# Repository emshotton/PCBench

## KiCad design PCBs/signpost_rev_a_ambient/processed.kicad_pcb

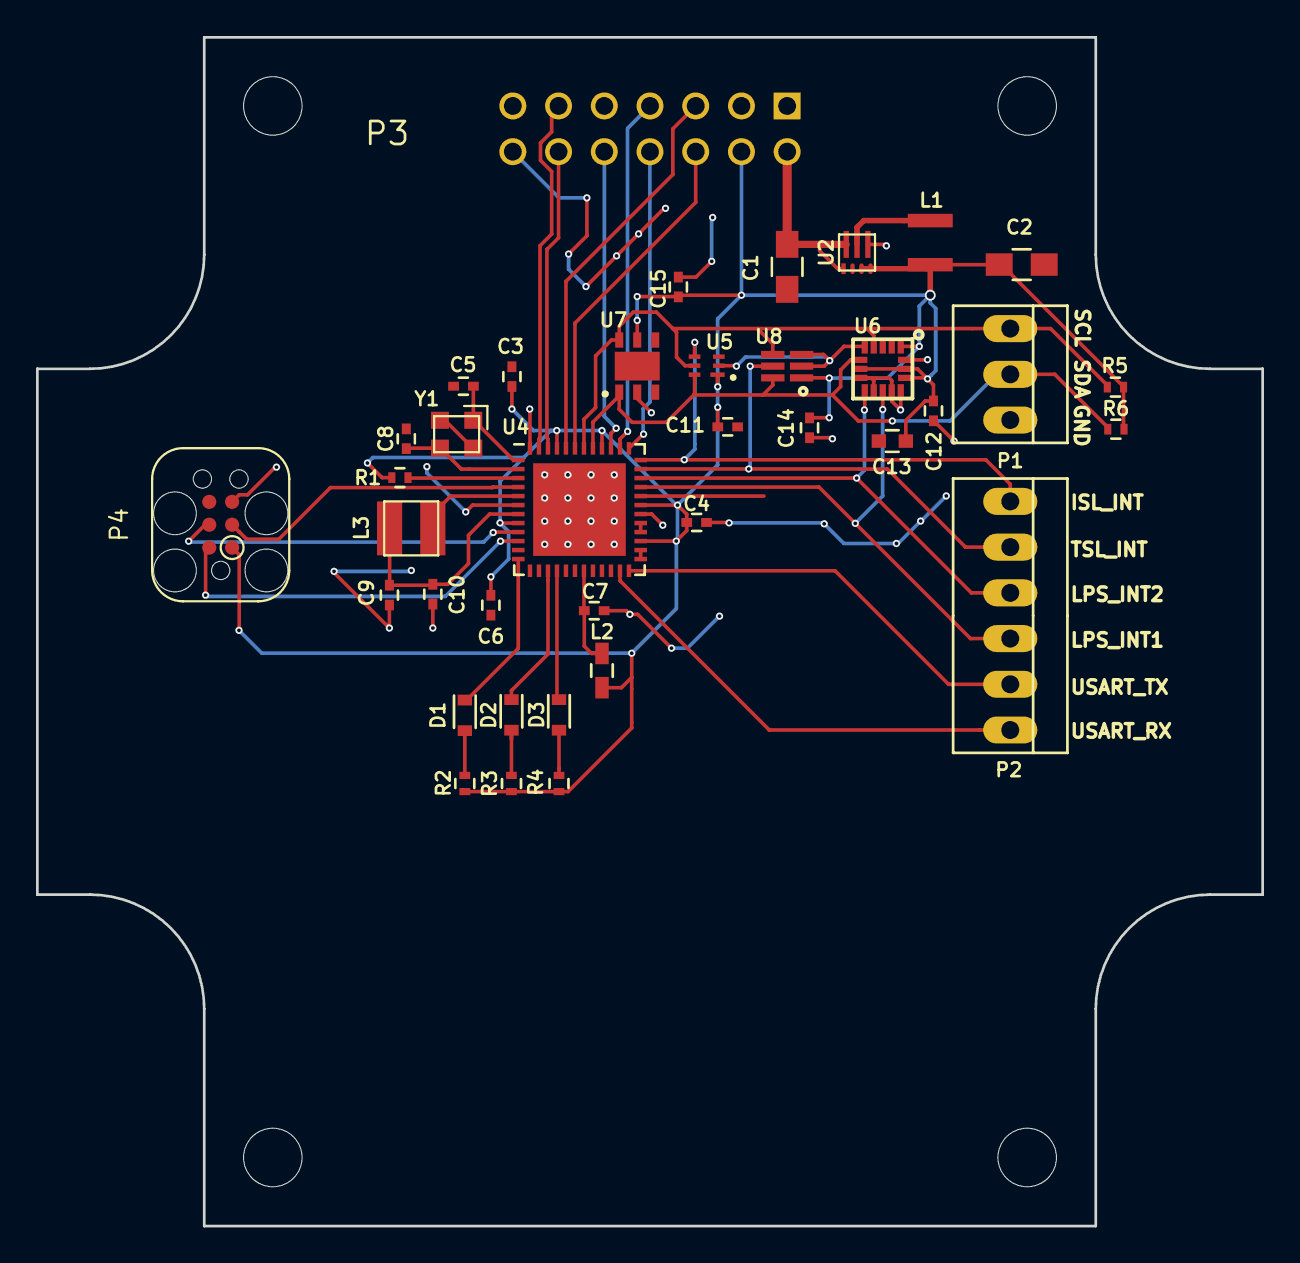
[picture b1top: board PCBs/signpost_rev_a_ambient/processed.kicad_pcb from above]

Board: 2 copper layers, 68.1 x 66.0 mm, 42 parts (0 on the bottom side), 36 nets.

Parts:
C1, C2: GENERIC_C_0805; C_0805_HandSoldering
C3, C4, C6, C7, C10, C11, C12, C14, C15: C_0.1u_0402_10V_10%_JB; C_0402
C5, C8: GENERIC_C_0402; C_0402
C9: C_4.7u_0402_10V_10%_X5R; C_0402
C13: C_10u_0603_10V_10%_JB; C_0603
D1, D2, D3: LED; D_0603
H1, H2, H3, H4: SIGNPOST_HOLE
L1: .47 uH; DFE322512C
L2: 1.5k Ohm; C_0603_HandSoldering
L3: 22uH; 1212
P1: CONN_01X03; PINHEAD1-3
P2: CONN_01X06; PINHEAD1-6
P3: SIGNPOST_MODULE_GENERIC
P4: JLINK-TC; TC2030-IDC
R1: R_10k_0402_1%,100ppm/c,0.063W; R_0402
R2, R3, R4, R5, R6: GENERIC_R_0402; R_0402
U2: TPS62086; RLT0007A
U4: SAM4LC8A; QFN-48-1EP_7x7mm_Pitch0.5mm
U5: ISL29035; L6_1.5x1.6mm
U6: LPS331AP; HCLGA-16L
U7: Si7021; DFN_3x3mm_1mm
U8: TSL2561; DFN2
Y1: FH1600015; FHXXX

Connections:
+3V3: C2.1, C3.1, C4.1, C6.1, C11.1, C12.1, C13.1, C14.1, C15.1, L1.1, L2.2, P3.4, P4.1, R1.1, R2.2, R3.2, R4.2, R5.1, R6.1, U2.3, U2.4, U4.8, U4.27, U4.31, U4.40, U4.45, U5.1, U6.1, U6.7, U6.14, U6.15, U7.5, U8.1
+5V: C1.1, P3.2, U2.1, U2.7
/CNTR_PPS: P3.7, U4.38
/CNTR_SCL: P3.5, U4.44
/CNTR_SDA: P3.6, U4.43
/ISL_INT: P2.1, U4.36, U5.4
/LED_1: D1.1, U4.12
/LED_2: D2.1, U4.15
/LED_3: D3.1, U4.16
/LPS_INT1: P2.4, U4.33, U6.11
/LPS_INT2: P2.3, U4.34, U6.9
/MOD_IN: P3.10, U4.39
/MOD_OUT: P3.8, U4.37
/SAM4L_RESET: P4.3, U4.4
/SAM4L_SWDCLK: P4.4, U4.9
/SAM4L_SWDIO: P4.2, U4.10
/TSL_INT: P2.2, U4.35, U8.5
/USART_RX: P2.6, U4.23
/USART_TX: P2.5, U4.24
/USB_D+: P3.11, U4.47
/USB_D-: P3.12, U4.46
/VDDANA: C7.1, L2.1, U4.19
/VDD_CORE: L3.1, U4.5
/VDD_OUT: C9.1, C10.1, L3.2, U4.7
/xin: C5.1, U4.1, Y1.1
/xout: C8.1, U4.2, Y1.3
GND: C1.2, C2.2, C3.2, C4.2, C5.2, C6.2, C7.2, C8.2, C9.2, C10.2, C11.2, C12.2, C13.2, C14.2, C15.2, P1.3, P3.1, P3.14, P4.5, U2.5, U4.6, U4.17, U4.30, U4.48, U4.49, U5.2, U6.5, U6.8, U6.10, U6.12, U6.13, U6.16, U7.2, U8.2, U8.3, Y1.2, Y1.4
unnamed: D1.2, R2.1
unnamed: D2.2, R3.1
unnamed: D3.2, R4.1
unnamed: L1.2, U2.6
unnamed: R1.2, U4.3
unnamed: U4.25, U4.26
unnamed: U4.28, U4.29
SCL: P1.1, R5.2, U4.42, U5.5, U6.4, U7.6, U8.4
SDA: P1.2, R6.2, U4.41, U5.6, U6.6, U7.1, U8.6

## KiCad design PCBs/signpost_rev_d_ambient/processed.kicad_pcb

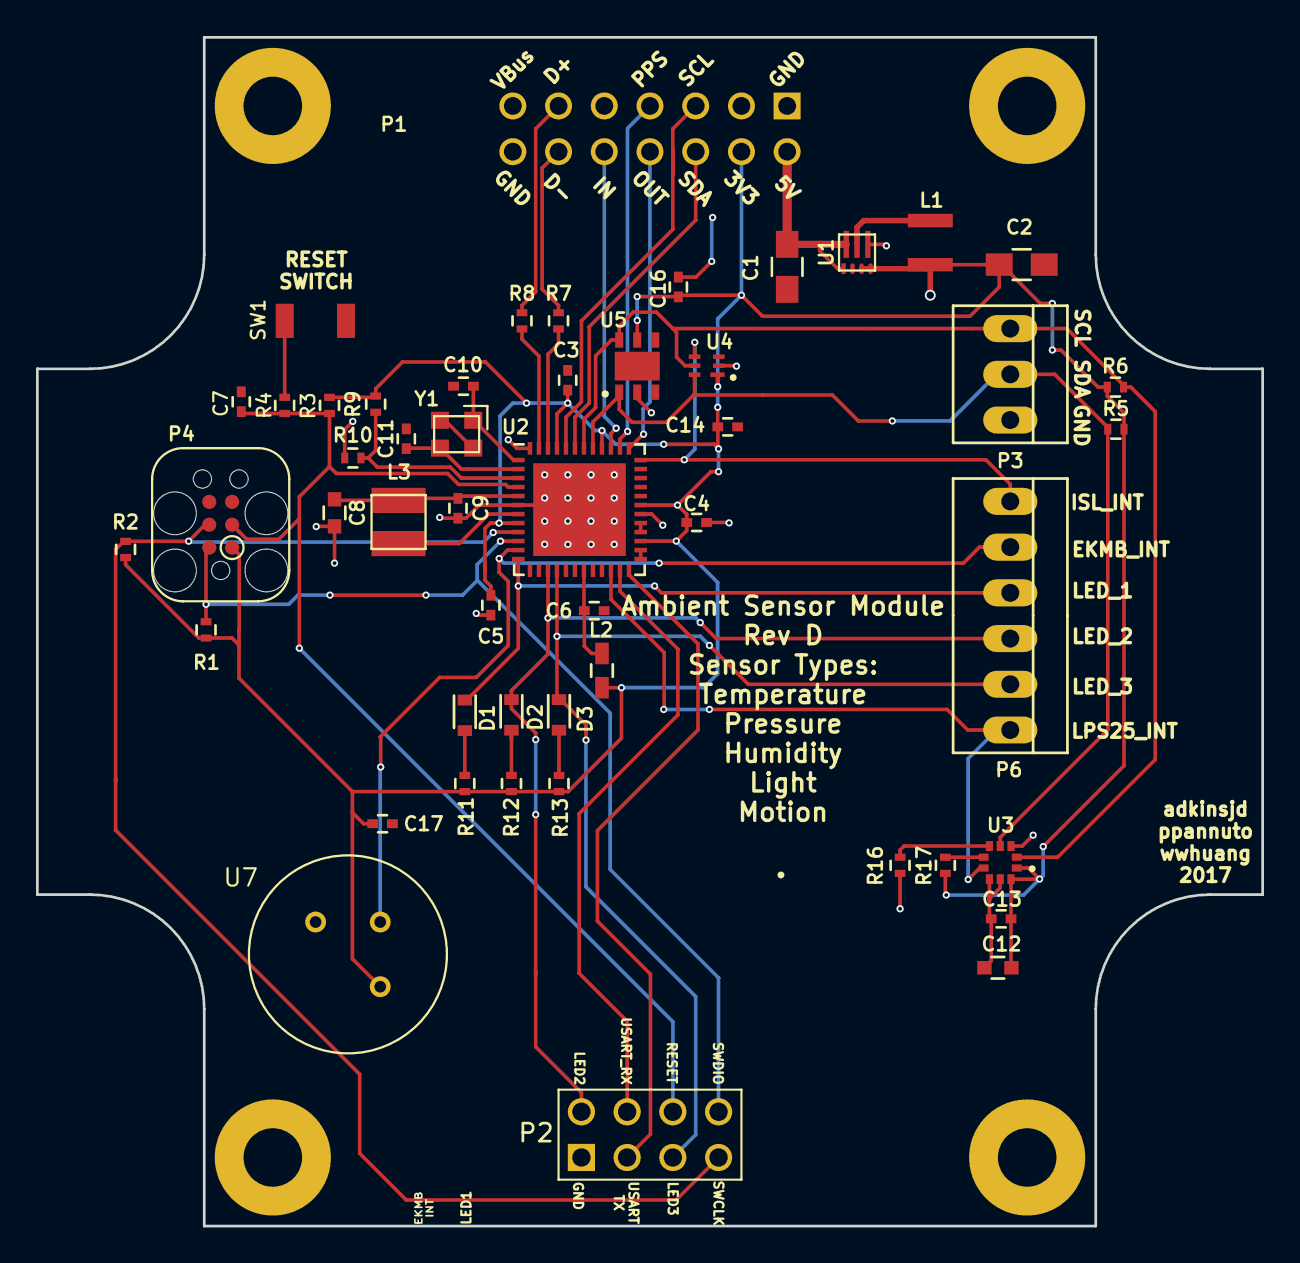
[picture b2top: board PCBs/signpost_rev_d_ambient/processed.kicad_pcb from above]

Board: 2 copper layers, 68.1 x 66.0 mm, 54 parts (0 on the bottom side), 40 nets.

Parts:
C1, C2: GENERIC_C_0805; C_0805_HandSoldering
C3, C4, C5, C6, C9, C13, C14, C16, C17: C_0.1u_0402_10V_10%_JB; C_0402
C7, C10, C11: GENERIC_C_0402; C_0402
C8: GENERIC_C_0603; C_0603
C12: C_10u_0603_10V_10%_JB; C_0603
D1, D2, D3: LED; D_0603
H1, H2, H3, H4: SIGNPOST_HOLE
L1: .47 uH; DFE322512C
L2: 1.5k Ohm; C_0603_HandSoldering
L3: 22uH; 1212
P1: SIGNPOST_MODULE_GENERIC
P2: CONN_02X04; PINHEAD2-4
P3: CONN_01X03; PINHEAD1-3
P4: JLINK-TC; TC2030-IDC
P6: CONN_01X06; PINHEAD1-6
R1, R2, R3, R16, R17: R_100K_0402_0.5%,25ppm/c,0.063W; R_0402
R4: GENERIC_R_0402; R_0402
R5, R6, R9: R_10k_0402_1%,100ppm/c,0.063W; R_0402
R7, R8: R_39_0402_1%,100ppm/c,0.063W; R_0402
R10: R_0_0402_.1W; R_0402
R11, R12, R13: R_1K_0402_1%,100ppm/c,0.2W; R_0402
SW1: BSU-1000P; B3U-1000p
U1: TPS62086; RLT0007A
U2: SAM4LC8A; QFN-48-1EP_7x7mm_Pitch0.5mm
U3: LPS25HB; HLGA-10L_2.5x2.5mm
U4: ISL29035; L6_1.5x1.6mm
U5: Si7021; DFN_3x3mm_1mm
U7: EKMB1101111
Y1: FH1600015; FHXXX

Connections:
+3V3: C2.1, C3.1, C4.1, C5.1, C12.1, C13.1, C14.1, C16.1, C17.1, L1.1, L2.2, P1.4, P4.1, R1.2, R2.1, R3.1, R5.1, R6.1, R9.1, R11.2, R12.2, R13.2, R17.1, U1.3, U1.4, U2.8, U2.27, U2.31, U2.40, U2.45, U3.1, U3.10, U4.1, U5.5, U7.2
+5V: C1.1, P1.2, U1.1, U1.7
/CNTR_PPS: P1.7, U2.38
/CNTR_SCL: P1.5, U2.44
/CNTR_SDA: P1.6, U2.43
/EKMB_INT: P6.2, U2.11, U7.1
/ISL_INT: P6.1, U2.36, U4.4
/LED_1: D1.1, P6.3, U2.12
/LED_2: D2.1, P2.2, P6.4, U2.15
/LED_3: D3.1, P2.5, P6.5, U2.16
/LPS25_INT: P6.6, U2.22, U3.7
/MOD_IN: P1.10, U2.39
/MOD_OUT: P1.8, U2.37
/SAM4L_RESET: C7.1, P2.6, P4.3, R3.2, R4.1, U2.4
/SAM4L_SWDCLK: P2.7, P4.4, R2.2, U2.9
/SAM4L_SWDIO: P2.8, P4.2, R1.1, U2.10
/USART_RX: P2.4, U2.23
/USART_TX: P2.3, U2.24
/USB_D+: P1.11, R8.2
/USB_D-: P1.12, R7.2
/VDDANA: C6.1, L2.1, U2.19
/VDD_CORE: C8.1, C9.1, L3.2, U2.5
/VDD_OUT: L3.1, U2.7
/sensors/LPS25_CS: R17.2, U3.6
/sensors/LPS25_SA0: R16.2, U3.5
/xin: C10.1, U2.1, Y1.1
/xout: C11.1, U2.2, Y1.3
GND: C1.2, C2.2, C3.2, C4.2, C5.2, C6.2, C7.2, C8.2, C9.2, C10.2, C11.2, C12.2, C13.2, C14.2, C16.2, C17.2, P1.1, P1.14, P2.1, P3.3, P4.5, R10.2, R16.1, SW1.2, U1.5, U2.6, U2.17, U2.30, U2.48, U2.49, U3.3, U3.8, U3.9, U4.2, U5.2, U7.3, Y1.2, Y1.4
unnamed: D1.2, R11.1
unnamed: D2.2, R12.1
unnamed: D3.2, R13.1
unnamed: L1.2, U1.6
unnamed: R4.2, SW1.1
unnamed: R7.1, U2.46
unnamed: R8.1, U2.47
unnamed: R9.2, R10.1, U2.3
unnamed: U2.25, U2.26
unnamed: U2.28, U2.29
SCL: P3.1, R6.2, U2.42, U3.2, U4.5, U5.6
SDA: P3.2, R5.2, U2.41, U3.4, U4.6, U5.1

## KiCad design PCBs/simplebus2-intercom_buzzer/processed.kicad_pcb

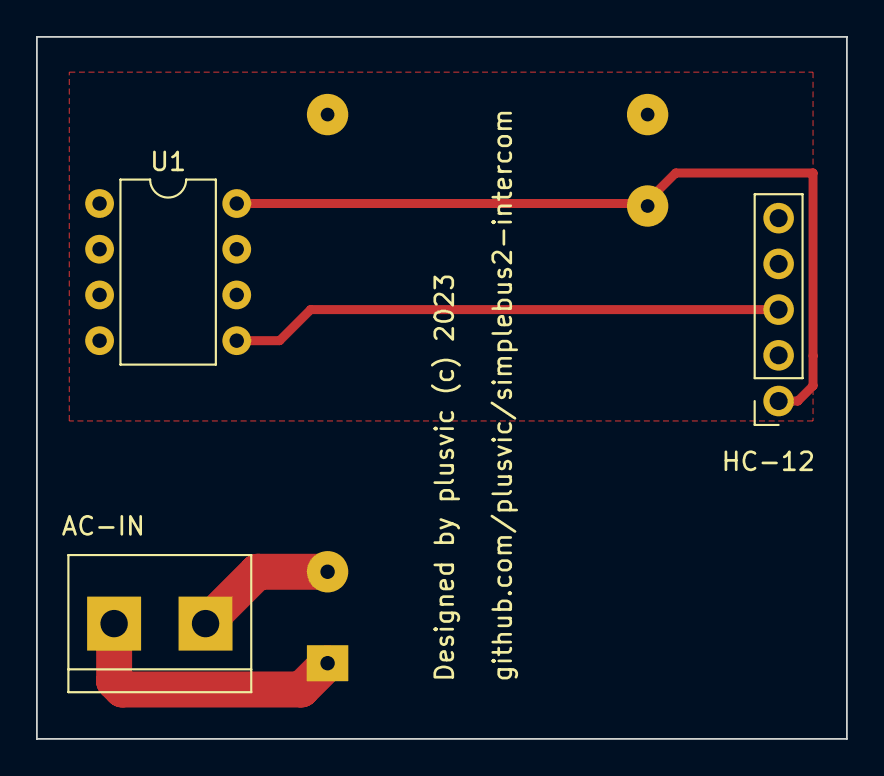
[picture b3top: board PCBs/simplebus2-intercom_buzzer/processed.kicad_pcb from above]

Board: 2 copper layers, 45.0 x 39.0 mm, 4 parts (1 on the bottom side), 5 nets.

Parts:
AC-IN: Screw_Terminal_01x02; TerminalBlock_bornier-2_P5.08mm
HC-12: Conn_01x05_Female; PinSocket_1x05_P2.54mm_Vertical
PS1: IRM-03-3.3; Custom_Converter_ACDC_MeanWell_IRM-03-xx_THT
U1: ATtiny13-20P; DIP-8_W7.62mm

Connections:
GND: HC-12.2, PS1.14 (-Vo), U1.4 (GND)
unnamed: HC-12.3, U1.5 (PB0)
unnamed: AC-IN.1, PS1.1 (AC/L)
unnamed: AC-IN.2, PS1.3 (AC/N)
Vcc: HC-12.1, PS1.16 (+Vo), U1.8 (VCC)

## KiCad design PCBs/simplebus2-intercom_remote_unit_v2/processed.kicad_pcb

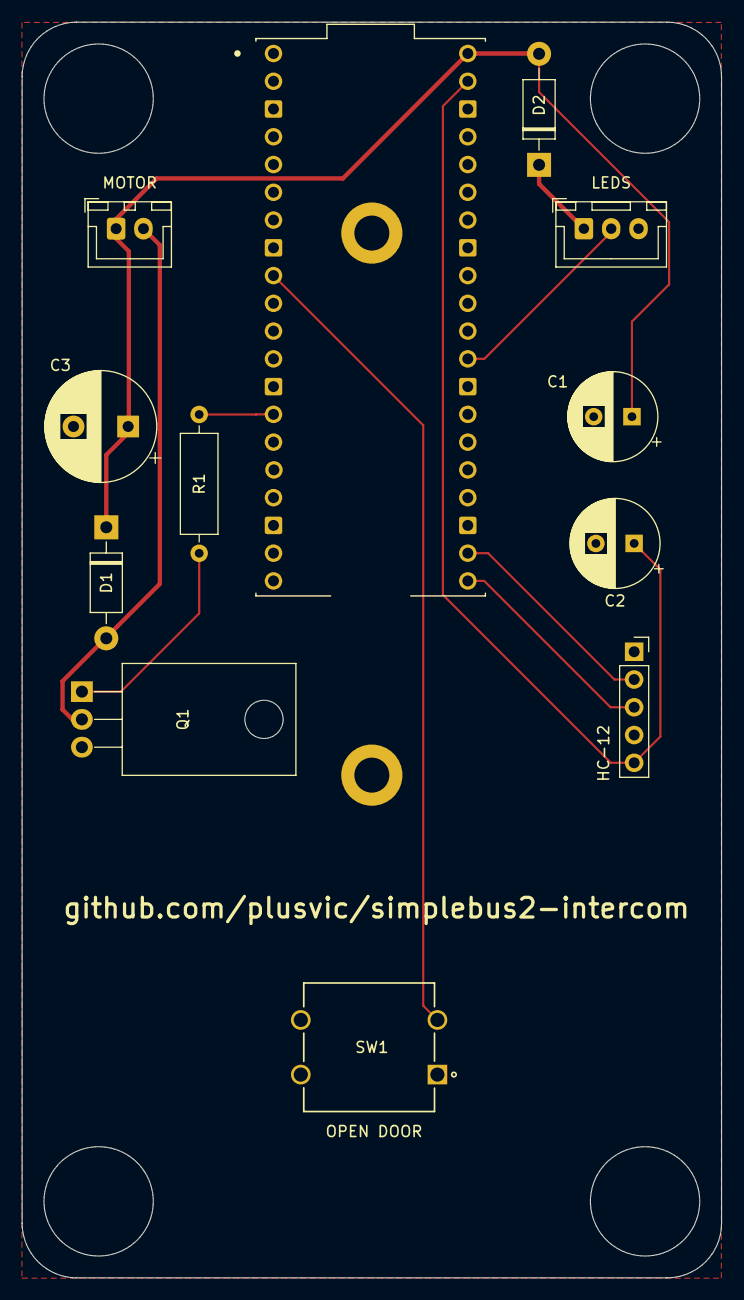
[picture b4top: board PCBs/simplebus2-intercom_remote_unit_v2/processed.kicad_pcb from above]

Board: 2 copper layers, 64.0 x 114.9 mm, 12 parts (0 on the bottom side), 11 nets.

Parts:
A1: SC0918; MODULE_SC0918
C1, C2: 470uF; CP_Radial_D8.0mm_P3.50mm
C3: 680uF; CP_Radial_D10.0mm_P5.00mm
D1, D2: 1N4001; D_DO-41_SOD81_P10.16mm_Horizontal
J1: LEDS; JST_XH_B3B-XH-A_1x03_P2.50mm_Vertical
J2: HC-12; PinSocket_1x05_P2.54mm_Vertical
J3: MOTOR; JST_XH_B2B-XH-A_1x02_P2.50mm_Vertical
Q1: Q_NPN_Darlington_BCE; TO-220-3_Horizontal_TabDown
R1: 1k; R_Axial_DIN0309_L9.0mm_D3.2mm_P12.70mm_Horizontal
SW1: OPEN DOOR; COM-10302_SPK

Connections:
3.3V: A1.39 (VSYS), C2.1, J2.5
/RX: A1.21 (GP16), J2.3
/TX: A1.22 (GP17), J2.2
GND: A1.3 (GND), A1.8 (GND), A1.13 (GND), A1.18 (GND), A1.23 (GND), A1.28 (GND), A1.33 (AGND), A1.38 (GND), C1.2, C2.2, C3.2, J1.3, J2.4, Q1.3 (E), SW1.1
unnamed: A1.9 (GP6), SW1.3 (K)
unnamed: A1.14 (GP10), R1.2
unnamed: A1.29 (GP22), J1.2
unnamed: D1.2 (A), J3.2, Q1.2 (C)
unnamed: D2.1 (K), J1.1
unnamed: Q1.1 (B), R1.1
VBUS: A1.40 (VBUS), C1.1, C3.1, D1.1 (K), D2.2 (A), J3.1

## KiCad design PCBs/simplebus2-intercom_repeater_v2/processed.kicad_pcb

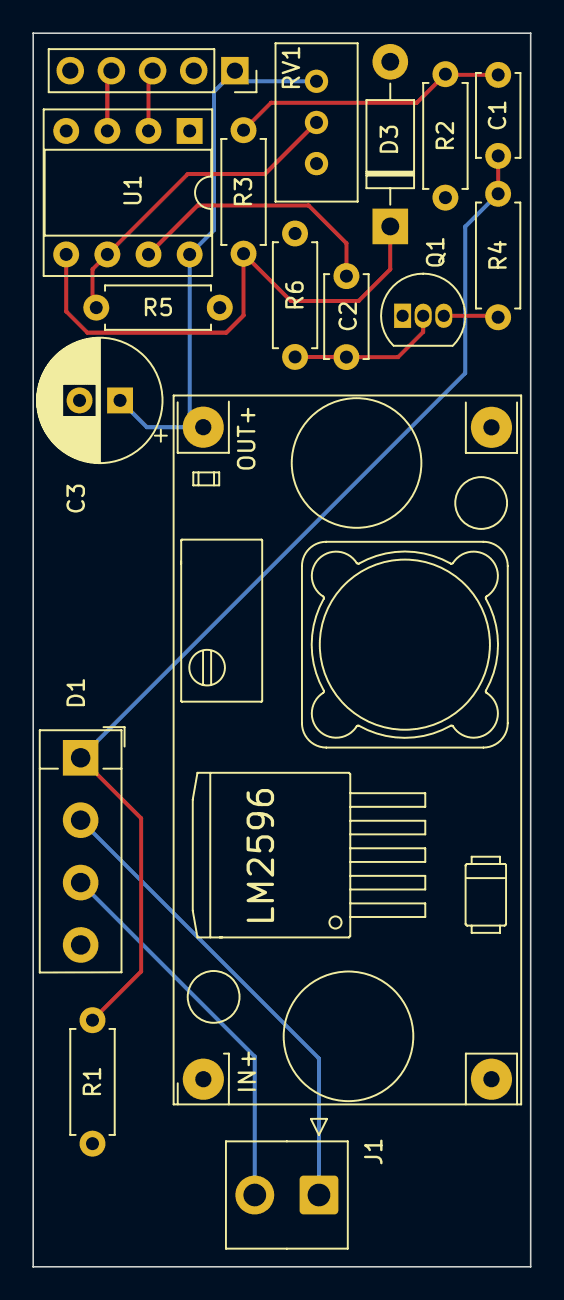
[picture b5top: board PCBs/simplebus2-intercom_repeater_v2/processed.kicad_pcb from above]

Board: 2 copper layers, 30.7 x 76.1 mm, 17 parts (0 on the bottom side), 13 nets.

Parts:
C1: 0.1uF; C_Disc_D5.0mm_W2.5mm_P5.00mm
C2: 100nF; C_Disc_D5.0mm_W2.5mm_P5.00mm
C3: 1000uF; CP_Radial_D7.5mm_P2.50mm
D1: Bridge Rectifier; Diode_Bridge_Vishay_KBPM
D3: 1N47xxA; D_DO-41_SOD81_P10.16mm_Horizontal
IN+: YAAJ_DCDC_StepDown_LM2596
J1: SimpleBus Connector; TE_826576-2_1x02_P3.96mm_Vertical
J2: HC-12; PinSocket_1x05_P2.54mm_Vertical
Q1: PN2222A; TO-92_Inline
R1: 560R; R_Axial_DIN0207_L6.3mm_D2.5mm_P7.62mm_Horizontal
R2, R5: 10k; R_Axial_DIN0207_L6.3mm_D2.5mm_P7.62mm_Horizontal
R3: 100; R_Axial_DIN0207_L6.3mm_D2.5mm_P7.62mm_Horizontal
R4: 220R; R_Axial_DIN0207_L6.3mm_D2.5mm_P7.62mm_Horizontal
R6: 2.2k; R_Axial_DIN0207_L6.3mm_D2.5mm_P7.62mm_Horizontal
RV1: 3298; Potentiometer_Bourns_3296W_Vertical
U1: ATtiny85-20P; DIP-8_W7.62mm_Socket

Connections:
+5V: C3.1, IN+.4, J2.1, RV1.1, U1.8 (VCC)
GND: C3.2, D1.4 (-), D3.2 (A), IN+.2, IN+.3, J2.2, Q1.1 (E), R2.2, R5.2, R6.2, U1.4 (GND)
unnamed: C1.2, R2.1, R3.2
unnamed: C1.1, D1.1 (+), R1.1, R4.1
unnamed: D3.1 (K), R3.1, U1.5 (AREF/PB0)
unnamed: D1.2, J1.1
unnamed: D1.3, J1.2
unnamed: C2.2, Q1.2 (B), R6.1
unnamed: Q1.3 (C), R4.2
unnamed: C2.1, U1.7 (PB2)
REF VOLTAGE: R5.1, RV1.2, U1.6 (PB1)
UART RX: J2.4, U1.3 (XTAL2/PB4)
UART TX: J2.3, U1.2 (XTAL1/PB3)

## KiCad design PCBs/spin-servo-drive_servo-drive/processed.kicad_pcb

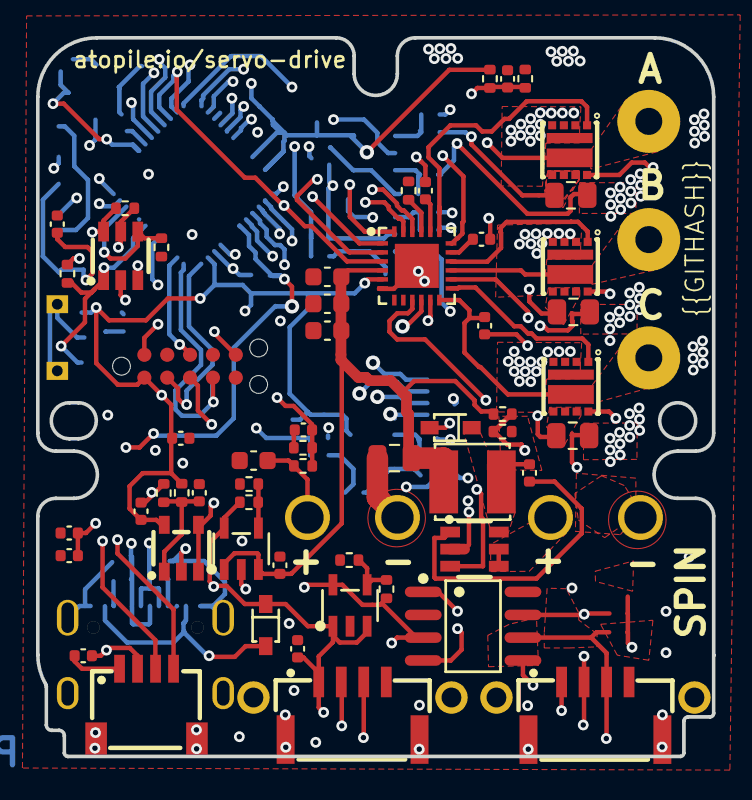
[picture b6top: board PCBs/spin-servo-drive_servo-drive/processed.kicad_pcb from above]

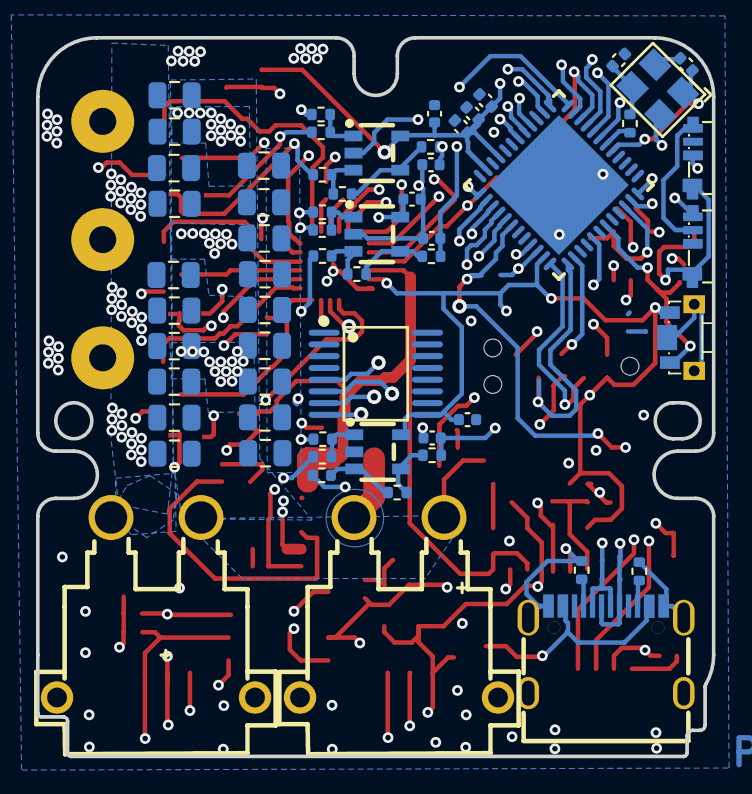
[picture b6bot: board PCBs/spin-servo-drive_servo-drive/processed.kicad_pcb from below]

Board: 4 copper layers, 37.6 x 39.9 mm, 125 parts (60 on the bottom side), 80 nets.

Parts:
C1: 10V 10uF X5R ±10% 0603 Multilayer Ceramic Capacit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; C0603
C2, C13, C16, C17, C18, C19, C24, C28, C40, C51: 16V 100nF X7R ±10% 0402 Multilayer Ceramic Capaci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; C0402
C3, C4, C6, C20, C21, C22, C25, C26, C27, C29, C30, C35, C36, C37, C38, C39, C47, C48, C49: C0805
C5, C7, C9, C14, C15, C33, C34, C41, C43, C45, C50: 25V 1uF X5R ±10% 0402 Multilayer Ceramic Capacito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; C0402
C8: 25V 10uF X5R ±10% 0805 Multilayer Ceramic Capacit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; C0805
C10, C11, C12: 50V 2.2nF X7R ±10% 0402 Multilayer Ceramic Capaci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; C0402
C23, C31, C32: 16V 4.7uF X5R ±10% 0603 Multilayer Ceramic Capaci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; C0603
C42, C44: 50V 22pF C0G ±5% 0402 Multilayer Ceramic Capacito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; C0402
J1: USB-C-SMD_KH-TYPE-C-16P
R1, R15, R20, R38: 62.5mW Thick Film Resistors 50V ±100ppm/℃ ±1% 10k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; R0402
R2, R6, R13, R25, R44, R48, R50: 62.5mW Thick Film Resistors 50V ±100ppm/℃ ±1% 1kΩ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; R0402
R3: 62.5mW Thick Film Resistors 50V ±100ppm/℃ ±1% 100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; R0402
R4, R8, R47: 3mΩ +/- 1%; R0805
R5, R9: 62.5mW Thick Film Resistors 50V ±100ppm/℃ ±1% 5.1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; R0402
R7: 62.5mW Thick Film Resistors 50V ±100ppm/℃ ±1% 200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; R0402
R10: 62.5mW Thick Film Resistors 50V ±100ppm/℃ ±1% 27.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; R0402
R11: 62.5mW Thick Film Resistors 50V ±100ppm/℃ ±1% 3kΩ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; R0402
R12, R14, R26, R45, R49, R51: 62.5mW Thick Film Resistors 50V ±100ppm/℃ ±1% 47k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; R0402
R16, R46, R52: 62.5mW Thick Film Resistors 50V -200ppm/℃~+500ppm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; R0402
R17: 62.5mW Thick Film Resistors 50V ±100ppm/℃ ±1% 20.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; R0402
R18: 62.5mW Thick Film Resistors 50V ±1% ±200ppm/℃ 6.3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; R0402
R19: 10kohm +/- 1%; R0402
R21: 62.5mW Thick Film Resistors 50V ±100ppm/℃ ±1% 11.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; R0402
R22: 62.5mW Thick Film Resistors 50V ±100ppm/℃ ±1% 6.2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; R0402
R29: 62.5mW Thick Film Resistors 50V ±100ppm/℃ ±1% 41.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; R0402
R30: 62.5mW Thick Film Resistors 50V ±100ppm/℃ ±1% 4.3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; R0402
R31: 62.5mW Thick Film Resistors 50V ±100ppm/℃ ±1% 43k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; R0402
U1, U3, U28: V-DFN3030-8K_L3.0-W3.0-P0.65-BL
U2, U14: CONN-TH_XT30PW-M
U4, U20, U21, U24: SOT-23-5_L3.0-W1.7-P0.95-LS2.8-BR
U5, U32: LED-SMD_4P-L4.0-W1.4_SK6805SIDE-S
U6, U18: SOT-23-6_L2.9-W1.6-P0.95-LS2.8-BR
U7, U8, U9: OutputPad
U10: IND-SMD_L4.0-W4.0
U11: KEY-SMD_SKTDLDE010
U12: VQFN-24_L4.0-W4.0-P0.50-TL-EP2.5
U13: UFQFPN-48_L7.0-W7.0-P0.50-BL-EP
U15: CONN-SMD_4P-P1.00_SM04B-SRSS-TB-LF-SN
U16: TAG-CONNECT_TC2050-IDC
U17, U19, U31, U33, U34, U35: NetTie-2_SMD_Pad0.25mm
U22, U23: SOT-23-5_L3.0-W1.7-P0.95-LS2.8-BL
U25: SOIC-8_L4.9-W3.9-P1.27-LS6.0-BL
U26, U27: CONN-SMD_4P-P1.25_SM04B-GHS-TB-LF-SN
U29: TSSOP-16_L5.0-W4.4-P0.65-LS6.4-BL
U30, U36: SOD-323_L1.8-W1.3-LS2.5-RD
U37: OSC-SMD_4P-L3.2-W2.5-BL

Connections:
anchor: U11.3, U11.4
canh: U25.7, U26.2, U27.2
canl: U25.6, U26.3, U27.3
cb: C24.1, U6.1
cc1: J1.A5, R5.1
cc2: J1.B5, R9.1
cs: U13.25, U29.8
dm: J1.A7, J1.B7, U13.33
dp: J1.A6, J1.B6, U13.34
ios.led1-vcc: U5.3, U32.4
micro-miso: U13.27, U29.5
micro-mosi: U13.28, U29.6
micro-sda: U13.30, U15.3
micro-vcc: U5.4, U13.29
micro-vcc-1: R20.2, U11.1, U13.43, U18.1
micro-vcc-2: C28.1, R15.2, R19.1, U13.12
micro-vcc-3: C19.1, R10.2, R11.1, U13.13
micro.micro-io: R2.1, U13.46, U18.4
micro.micro-io-1: R3.1, U13.14, U18.6
micro.micro.ic-vcc-1: C42.1, U13.5, U37.1
pf1_osc_out: R7.1, U13.6
power_stage-gnd: C1.2, C2.2, C3.2, C4.2, C5.2, C6.2, C7.2, C8.2, C9.2, C10.2, C11.2, C12.2, C13.2, C14.2, C15.2, C16.2, C17.2, C18.2, C19.2, C20.2, C21.2, C22.2, C23.2, C25.2, C26.2, C27.2, C28.2, C29.2, C30.2, C31.2, C32.2, C33.2, C34.2, C35.2, C36.2, C37.2, C38.2, C39.2, C40.2, C42.2, C44.2, C47.2, C48.2, C49.2, C50.2, C51.2, J1.1, J1.2, J1.3, J1.4, J1.A1, J1.A12, J1.B1, J1.B12, R2.2, R4.2, R5.2, R8.2, R9.2, R11.2, R18.2, R19.2, R20.1, R22.2, R30.2, R31.2, R38.2, R47.2, U2.1, U2.3, U2.4, U4.2, U5.2, U6.2, U12.6, U12.25, U13.49, U14.1, U14.3, U14.4, U15.1, U15.5, U15.6, U16.3, U16.5, U18.2, U19.2, U20.2, U21.2, U22.2, U23.2, U24.2, U25.2, U25.8, U26.4, U26.5, U26.6, U27.4, U27.5, U27.6, U29.4, U29.11, U29.12, U29.13, U32.2, U33.2, U35.2, U36.2, U37.2, U37.4
power_stage-vcc: C1.1, C3.1, C4.1, C6.1, C20.1, C21.1, C22.1, C25.1, C26.1, C27.1, C29.1, C30.1, C35.1, C36.1, C37.1, C38.1, C39.1, C47.1, C48.1, C49.1, R10.1, U1.2, U1.3, U1.4, U1.10, U2.2, U3.2, U3.3, U3.4, U3.10, U6.4, U6.5, U14.2, U28.2, U28.3, U28.4, U28.10
power_stage-vcc-1: C5.1, C8.1, C23.1, C31.1, C32.1, R29.1, U10.2, U12.4, U22.1, U22.3
power_stage-vcc-2: C7.1, C13.1, C15.1, C16.1, C17.1, C18.1, C40.1, C50.1, C51.1, R1.1, R3.2, R15.1, R21.1, U4.5, U11.2, U12.5, U13.20, U13.21, U13.23, U13.35, U13.48, U15.2, U16.1, U18.5, U20.5, U21.5, U23.5, U24.5, U25.3, U29.9
power_stage.gate_driver.ic-vcc: C41.1, U12.20
power_stage.gate_driver.ic-vcc-1: C43.1, U12.17
power_stage.gate_driver.ic-vcc-2: C45.1, U12.14
power_stage.gate_driver.ic-vcc-3: R31.1, U12.21
power_stage.phase_a-vcc: U12.1, U12.22, U13.8
power_stage.phase_a.current_sensor-vcc: R14.2, R45.2, R51.2, U4.3, U4.4
power_stage.phase_a.current_sensor-vcc-1: C10.1, R16.2, U13.17
power_stage.phase_a.current_sensor.net_tie_n-_shunt_n: R6.1, U19.1
power_stage.phase_a.current_sensor.net_tie_p-_shunt_p: R13.1, U17.1
power_stage.phase_a.current_sensor.opamp-gnd: R12.2, R16.1, U20.4
power_stage.phase_a.current_sensor.opamp-inverting: R6.2, R12.1, U20.3
power_stage.phase_a.current_sensor.opamp-non_inverting: R13.2, R14.1, U20.1
power_stage.phase_a.half_bridge-gnd: R4.1, U17.2, U28.5, U28.6, U28.7
power_stage.phase_a.half_bridge-io: C41.2, U7.1, U12.18, U28.9
power_stage.phase_a.half_bridge-vcc: U12.19, U28.1
power_stage.phase_a.half_bridge-vcc-1: U12.11, U28.8
power_stage.phase_b-vcc: U12.2, U12.23, U13.9
power_stage.phase_b.current_sensor-vcc: C11.1, R46.2, U13.18
power_stage.phase_b.current_sensor.net_tie_n-_shunt_n: R25.1, U33.1
power_stage.phase_b.current_sensor.net_tie_p-_shunt_p: R44.1, U31.1
power_stage.phase_b.current_sensor.opamp-gnd: R26.2, R46.1, U21.4
power_stage.phase_b.current_sensor.opamp-inverting: R25.2, R26.1, U21.3
power_stage.phase_b.current_sensor.opamp-non_inverting: R44.2, R45.1, U21.1
power_stage.phase_b.half_bridge-gnd: R8.1, U1.5, U1.6, U1.7, U31.2
power_stage.phase_b.half_bridge-io: C43.2, U1.9, U8.1, U12.15
power_stage.phase_b.half_bridge-vcc: U1.1, U12.16
power_stage.phase_b.half_bridge-vcc-1: U1.8, U12.10
power_stage.phase_c-vcc: U12.3, U12.24, U13.10
power_stage.phase_c.current_sensor-vcc: C12.1, R52.2, U13.11
power_stage.phase_c.current_sensor.net_tie_n-_shunt_n: R48.1, U35.1
power_stage.phase_c.current_sensor.net_tie_p-_shunt_p: R50.1, U34.1
power_stage.phase_c.current_sensor.opamp-gnd: R49.2, R52.1, U24.4
power_stage.phase_c.current_sensor.opamp-inverting: R48.2, R49.1, U24.3
power_stage.phase_c.current_sensor.opamp-non_inverting: R50.2, R51.1, U24.1
power_stage.phase_c.half_bridge-gnd: R47.1, U3.5, U3.6, U3.7, U34.2
power_stage.phase_c.half_bridge-io: C45.2, U3.9, U9.1, U12.12
power_stage.phase_c.half_bridge-vcc: U3.1, U12.13
power_stage.phase_c.half_bridge-vcc-1: U3.8, U12.9
power_stage.voltage_reference.opamp-non_inverting: C2.1, R1.2, R38.1, U4.1
power_supply-vcc: J1.A4, J1.A9, J1.B4, J1.B9, U30.2
power_supply-vcc-1: C9.1, C14.1, C33.1, C34.1, R17.1, U5.1, U22.5, U23.1, U23.3, U26.1, U27.1, U30.1, U32.1
power_supply.buck.feedback_div-out: R29.2, R30.1, U6.3
power_supply.ldo3V3.feedback_div-out: R21.2, R22.1, U23.4
power_supply.ldo5V.feedback_div-out: R17.2, R18.1, U22.4
reset: U13.7, U16.10
rx: U18.3, U25.4
sck: U13.26, U29.7
scl: U13.16, U15.4
sw: C24.2, U6.6, U10.1, U36.1
tck: U13.37, U16.4
tdi: U13.38, U16.8
tdo: U13.41, U16.6
tms: U13.36, U16.2
tx: U13.47, U25.1
xout: C44.1, R7.2, U37.3

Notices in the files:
PCBs/simplebus2-intercom_buzzer/processed.kicad_pcb:
Designed by plusvic (c) 2023
